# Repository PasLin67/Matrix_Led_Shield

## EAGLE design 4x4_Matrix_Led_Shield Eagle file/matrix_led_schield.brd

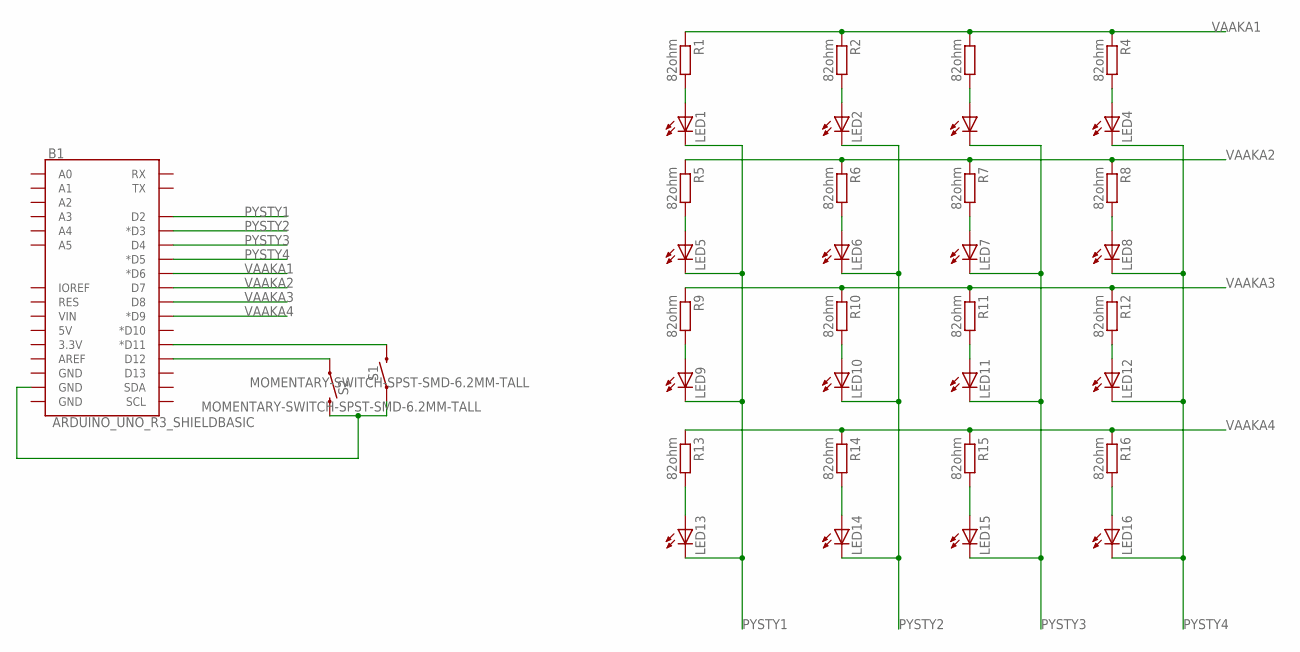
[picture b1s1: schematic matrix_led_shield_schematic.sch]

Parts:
B1: ARDUINO_UNO_R3_SHIELDBASIC; UNO_R3_SHIELD
LED1, LED2, LED3, LED4, LED5, LED6, LED7, LED8, LED9, LED10, LED11, LED12, LED13, LED14, LED15, LED16: LG_T679-E1F1-1; PLCC2
R1, R2, R3, R4, R5, R6, R7, R8, R9, R10, R11, R12, R13, R14, R15, R16: 82ohm; M0805
S1, S2: MOMENTARY-SWITCH-SPST-SMD-6.2MM-TALL; TACTILE_SWITCH_SMD_6.2MM_TALL

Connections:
unnamed: B1.D12, S2.A2 (1)
unnamed: B1.D11 (*D11), S1.B2 (2)
unnamed: B1.GND@1 (GND), S1.A2 (1), S2.B2 (2)
unnamed: LED1.A, R1.2
unnamed: LED2.A, R2.2
unnamed: LED3.A, R3.2
unnamed: LED4.A, R4.2
unnamed: LED5.A, R5.2
unnamed: LED6.A, R6.2
unnamed: LED7.A, R7.2
unnamed: LED8.A, R8.2
unnamed: LED9.A, R9.2
unnamed: LED10.A, R10.2
unnamed: LED11.A, R11.2
unnamed: LED12.A, R12.2
unnamed: LED13.A, R13.2
unnamed: LED14.A, R14.2
unnamed: LED15.A, R15.2
unnamed: LED16.A, R16.2
PYSTY1: B1.D2, LED1.C, LED5.C, LED9.C, LED13.C
PYSTY2: B1.D3 (*D3), LED2.C, LED6.C, LED10.C, LED14.C
PYSTY3: B1.D4, LED3.C, LED7.C, LED11.C, LED15.C
PYSTY4: B1.D5 (*D5), LED4.C, LED8.C, LED12.C, LED16.C
VAAKA1: B1.D6 (*D6), R1.1, R2.1, R3.1, R4.1
VAAKA2: B1.D7, R5.1, R6.1, R7.1, R8.1
VAAKA3: B1.D8, R9.1, R10.1, R11.1, R12.1
VAAKA4: B1.D9 (*D9), R13.1, R14.1, R15.1, R16.1

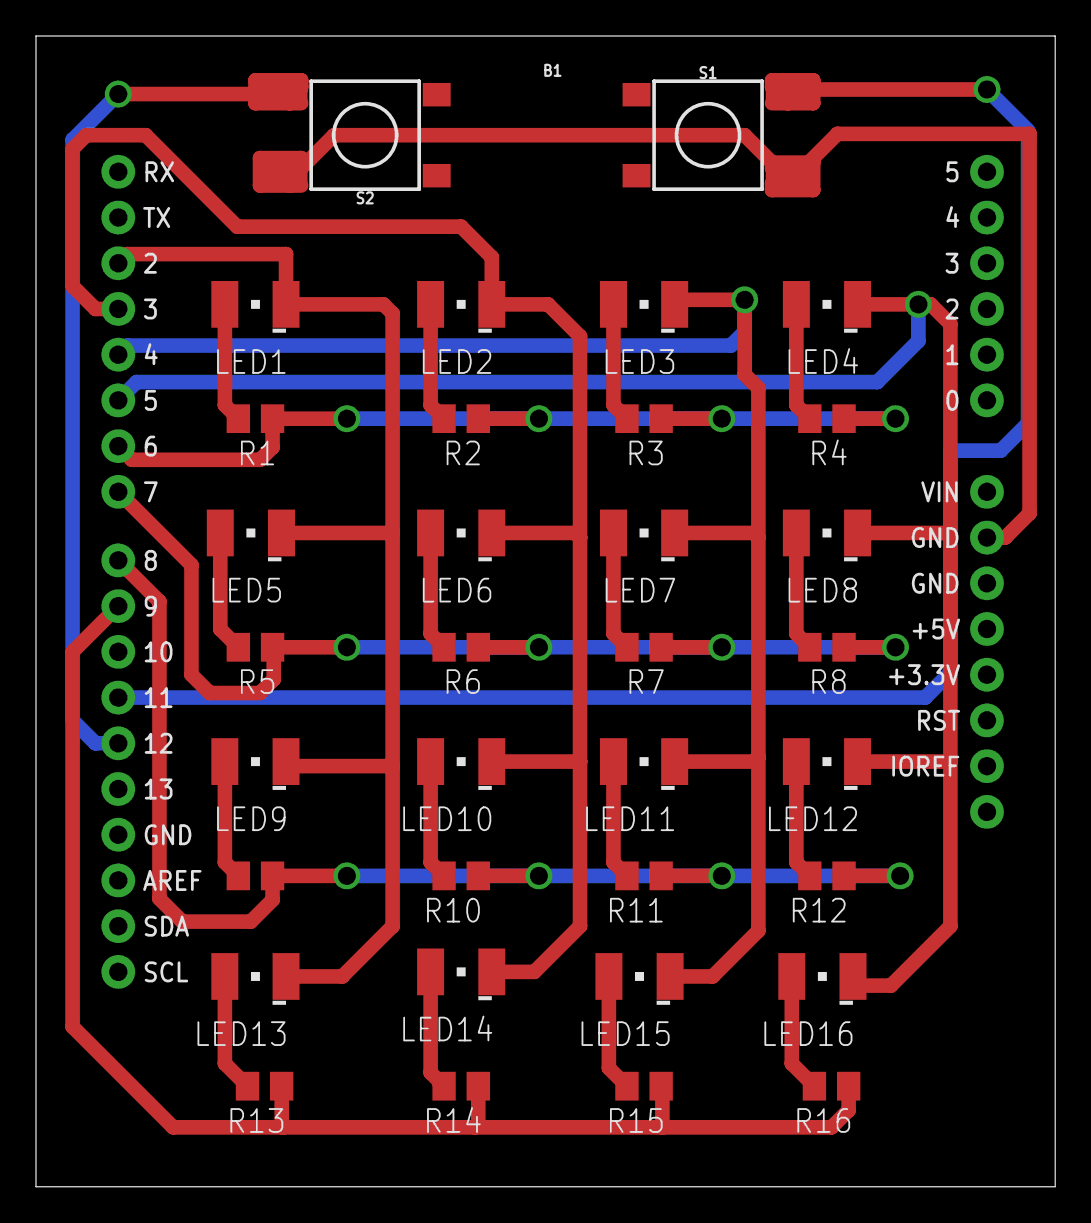
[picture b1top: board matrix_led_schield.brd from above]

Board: 2 copper layers, 56.6 x 63.9 mm, 35 parts (0 on the bottom side), 27 nets.

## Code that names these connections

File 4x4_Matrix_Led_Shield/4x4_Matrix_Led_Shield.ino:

#define Vaaka1 6  // led1,led2,led3,led4
#define Vaaka2 7  // led5,led6,led7,led8
#define Vaaka3 8  // led9,led10,led11,led12
#define Vaaka4 9  // led13,led14,led15,led16
#define Pysty1 2  // led1,led5,led9,led13
#define Pysty2 3  // led2,led6,led10,led14
#define Pysty3 4  // led3,led7,led11,led15
#define Pysty4 5  // led4,led8,led12,led1
#define WAIT 500
#define viive 300


const int S1 = 11; // Arduinoon liitetty pinni
const int S2 = 12; // Arduinoon liitetty pinni
const int NAPPIPOHJASSA = LOW;

void setup() {
  
 pinMode(Vaaka1, OUTPUT);
 pinMode(Vaaka1, OUTPUT);
 pinMode(Vaaka3, OUTPUT);
 pinMode(Vaaka4, OUTPUT);
 pinMode(Pysty1, OUTPUT);
 pinMode(Pysty2, OUTPUT);
 pinMode(Pysty3, OUTPUT);
 pinMode(Pysty4, OUTPUT);
 pinMode(S1, INPUT_PULLUP);
 pinMode(S2, INPUT_PULLUP);

}
void ledOff(){   // Sammuttaa kaikki ledit
  digitalWrite(Vaaka1, LOW);
  digitalWrite(Vaaka2, LOW);
  digitalWrite(Vaaka3, LOW);
  digitalWrite(Vaaka4, LOW);
  digitalWrite(Pysty1, HIGH);
  digitalWrite(Pysty2, HIGH);
  digitalWrite(Pysty3, HIGH);
  digitalWrite(Pysty4, HIGH);
}

void ledOn(){   // Sytyttää kaikki ledit
  digitalWrite(Vaaka1, HIGH);
  digitalWrite(Vaaka2, HIGH);
  digitalWrite(Vaaka3, HIGH);
  digitalWrite(Vaaka4, HIGH);
  digitalWrite(Pysty1, LOW);
  digitalWrite(Pysty2, LOW);
  digitalWrite(Pysty3, LOW);
  digitalWrite(Pysty4, LOW);
}


void spiraali(){
   ledOff(); 
   Led1();
   delay(viive);
   ledOff();
   Led2();
   delay(viive);
   ledOff();
   Led3();
   delay(viive);
   ledOff();
   Led4();
   delay(viive);
   ledOff();
   Led8();
   delay(viive);
   ledOff();
   Led12();
   delay(viive);
   ledOff();
   Led16();
   delay(viive);
   ledOff();
   Led15();
   delay(viive);
   ledOff();
   Led14();
   delay(viive);
   ledOff();
   Led13();
   delay(viive);
   ledOff();
   Led9();
   delay(viive);
   ledOff();
   Led5();
   delay(viive);
   ledOff();
   Led6();
   delay(viive);
   ledOff();
   Led7();
   delay(viive);
   ledOff();
   Led11();
   delay(viive);
   ledOff();
   Led10();
   delay(viive);
   ledOn();
   delay(WAIT);
   ledOff();
    Led10();
   delay(WAIT);
   ledOff();
   Led11();
   delay(WAIT);
   ledOff();
   Led7();
   delay(WAIT);
   ledOff();
   Led6();
   delay(WAIT);
   ledOff();
   Led5();
   delay(WAIT);
   ledOff();
   Led9();
   delay(WAIT);
   ledOff();
   Led13();
   delay(WAIT);
   ledOff();
   Led14();
   delay(WAIT);
   ledOff();
   Led15();
   delay(WAIT);
   ledOff();
   Led16();
   delay(WAIT);
   ledOff();
   Led12();
   delay(WAIT);
   ledOff();
   Led8();
   delay(WAIT);
   ledOff();
   Led4();
   delay(WAIT);
   ledOff();
   Led3();
   delay(WAIT);
   ledOff();
   Led2();
   delay(WAIT);
   ledOff();
   Led1();
   delay(WAIT);
   ledOn();
   delay(WAIT);
   ledOff();
   Led1();
   delay(200);
   ledOff();
   Led16();
   delay(200);
   ledOff();
   Led4();
   delay(200);
   ledOff();
   Led13();
   delay(200);
   ledOff();
}

void kulmat(){
  Led1();
  delay(200);
  ledOff();
  Led16();
  delay(200);
  ledOff();
  Led4();
  delay(200);
  ledOff();
  Led13();
  delay(200);
  ledOff();
 }
 void rivit(){
  ledOff();
  digitalWrite(Vaaka1, HIGH);
  digitalWrite(Pysty1, LOW);
  digitalWrite(Vaaka1, HIGH);
  digitalWrite(Pysty2, LOW);
  digitalWrite(Vaaka1, HIGH);
  digitalWrite(Pysty3, LOW);
  digitalWrite(Vaaka1, HIGH);
  digitalWrite(Pysty4, LOW);
  delay(WAIT); 
  ledOff();
  digitalWrite(Vaaka2, HIGH);
  digitalWrite(Pysty1, LOW);
  digitalWrite(Vaaka2, HIGH);
  digitalWrite(Pysty2, LOW);
  digitalWrite(Vaaka2, HIGH);
  digitalWrite(Pysty3, LOW);
  digitalWrite(Vaaka2, HIGH);
  digitalWrite(Pysty4, LOW);
  delay(WAIT);
  ledOff();
  digitalWrite(Vaaka3, HIGH);
  digitalWrite(Pysty1, LOW);
  digitalWrite(Vaaka3, HIGH);
  digitalWrite(Pysty2, LOW);
  digitalWrite(Vaaka3, HIGH);
  digitalWrite(Pysty3, LOW);
  digitalWrite(Vaaka3, HIGH);
  digitalWrite(Pysty4, LOW);
  delay(WAIT);
  ledOff();
  digitalWrite(Vaaka4, HIGH);
  digitalWrite(Pysty1, LOW);
  digitalWrite(Vaaka4, HIGH);
  digitalWrite(Pysty2, LOW);
  digitalWrite(Vaaka4, HIGH);
  digitalWrite(Pysty3, LOW);
  digitalWrite(Vaaka4, HIGH);
  digitalWrite(Pysty4, LOW);
  delay(WAIT);
 }

void Led1(){
  digitalWrite(Vaaka1, HIGH);
  digitalWrite(Pysty1, LOW);
 }
void Led2(){
  digitalWrite(Vaaka1, HIGH);
  digitalWrite(Pysty2, LOW);
 }
void Led3(){
  digitalWrite(Vaaka1, HIGH);
  digitalWrite(Pysty3, LOW);
 }
void Led4(){
  digitalWrite(Vaaka1, HIGH);
  digitalWrite(Pysty4, LOW);
 }
void Led5(){
  digitalWrite(Vaaka2, HIGH);
  digitalWrite(Pysty1, LOW);
 }
void Led6(){
  digitalWrite(Vaaka2, HIGH);
  digitalWrite(Pysty2, LOW);
  }
void Led7(){
  digitalWrite(Vaaka2, HIGH);
  digitalWrite(Pysty3, LOW);
  
 }
void Led8(){
  digitalWrite(Vaaka2, HIGH);
  digitalWrite(Pysty4, LOW);
  
 }
void Led9(){
  digitalWrite(Vaaka3, HIGH);
  digitalWrite(Pysty1, LOW);
  
 }
void Led10(){
  digitalWrite(Vaaka3, HIGH);
  digitalWrite(Pysty2, LOW);
  
 }
void Led11(){
  digitalWrite(Vaaka3, HIGH);
  digitalWrite(Pysty3, LOW);
  
 }
void Led12(){
  digitalWrite(Vaaka3, HIGH);
  digitalWrite(Pysty4, LOW);
  
 }
void Led13(){
  digitalWrite(Vaaka4, HIGH);
  digitalWrite(Pysty1, LOW);
  
 }
void Led14(){
  digitalWrite(Vaaka4, HIGH);
  digitalWrite(Pysty2, LOW);
 
 }
void Led15(){
  digitalWrite(Vaaka4, HIGH);
  digitalWrite(Pysty3, LOW);
  
 }
void Led16(){
  digitalWrite(Vaaka4, HIGH);
  digitalWrite(Pysty4, LOW);
  
 }

   
void loop(){

 int tilaS1 = digitalRead(S1);
 int tilaS2 = digitalRead(S2);

 if (tilaS1 == NAPPIPOHJASSA){
 spiraali();
 }else{
  ledOff();
}

 if (tilaS2 == NAPPIPOHJASSA) {
  rivit();
 }else{
  ledOff();
 }

}

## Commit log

2018-12-17 Näyttötyön dokumentit

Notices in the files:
parts and their libraries:
SparkFun-Boards: Licensing: Creative Commons ShareAlike 4.0 International - https://creativecommons.org/licenses/by-sa/4.0
